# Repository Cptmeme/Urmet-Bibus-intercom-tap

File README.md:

# telefoon_input: Urmet Bibus VOP intercom tap

Reverse-engineering the Urmet intercom (Artico monitor 1705/1 on bracket 1705/954,
Bibus 2nd Ed. VOP) so it can be bridged into Home Assistant.

| Path | What |
|---|---|
| `bus_tap/` | KiCad project for the analog tap board (L1/L2 + C1/C2 to ESP32 ADC), JLCPCB files in `bus_tap/jlc/` |
| `firmware/bus_tap_capture/` | ESP32 firmware streaming the tap's ADC channels over Wi-Fi/UDP |
| `host/` | `bustap`: record, analyse, decode and compare bus traffic |
| `docs/` | Urmet Bibus 2nd Ed. VOP technical manual, section 4B |
| `telefoon_input.kicad_sch` | reverse-engineered schematic of the AliExpress PC817 opto board |

Order of work: build the tap board, flash the firmware, run `bustap monitor` at the wall,
then record and decode. See `host/README.md`.

**Safety.** bus_tap GND is bus L2 and the tap is not isolated. While it is connected to
the intercom, the ESP32 runs from an isolated USB supply and talks over Wi-Fi only.

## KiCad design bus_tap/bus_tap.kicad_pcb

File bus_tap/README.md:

# Urmet Bibus VOP — L1/L2 + C1/C2 analog tap

Front end that lets an ESP32 act as the oscilloscope we don't have, so we can
measure the modulation depth and bit timing on the Urmet door-phone bus.

Target hardware: **Urmet Bibus 2nd Ed. VOP**, Artico monitor Ref. 1705/1 on
bracket Ref. 1705/954. Manual in `../docs/`.

## Wiring

### Intercom side
| Board | Intercom terminal | Note |
|---|---|---|
| J1-1 | **L1** | bus positive (22.5 V idle as measured) |
| J1-2 | **L2** | becomes board GND |
| J2-1 | **C1** | floor call |
| J2-2 | **C2** | floor call |

Leave **VPI / VPU alone.** They carry the monitor's operating power
(700 mA, 16–18.5 Vdc), not just video.

### ESP32 side — J3
| J3 | ESP32 (classic DevKit) | Signal |
|---|---|---|
| 1 | 3V3 | supply for U1 |
| 2 | GND | **= bus L2** |
| 3 | GPIO34 | `ADC_DC`  — channel A, absolute bus voltage |
| 4 | GPIO35 | `ADC_AC`  — channel B, AC-coupled ×11 |
| 5 | GPIO36 (VP) | `ADC_FC` — channel C, floor call |

**Use ADC1 pins only.** ADC2 is unusable while Wi-Fi is on, and we need Wi-Fi
(see safety note below). GPIO34/35/36 are input-only, which suits analog.

## Channels

- **A — absolute.** R1/R2 divide by 11, U1A buffers, R3/C1 anti-alias at ~16 kHz.
  Window 0–34 V, so 22.5 V idle sits at 2.05 V. Shows big dips and the DC level.
- **B — AC-coupled, gain 11.** C2 blocks DC, R4/R5 re-bias to 1.65 V, U1B gains
  ×11. Net effect: **1 V of bus swing = 1 V at the ADC**, centred on 1.65 V,
  ±1.5 V before clipping, 3.2 Hz high-pass. This is the channel that will show
  small modulation and edges that channel A buries in quantisation noise.
- **C — floor call.** Same divider + buffer on C1/C2.

MCP6004 is CMOS (~1 pA bias), so the 1 MΩ divider costs ~1 µV of offset. Do not
substitute a bipolar op-amp such as LM324 — it is neither rail-to-rail nor
happy at 3.3 V, and its bias current would swamp the divider.

## Connector notes

There is **no separate external GND**. Board GND *is* bus L2 - it arrives on J1-2 and
leaves on J3-2 to the ESP32. Do not add a dedicated ground pin; the one thing this
board must not have is two references.

Mis-plugging is harmless: both bus channels use identical 1M/100k front ends, so
swapping the L1/L2 and C1/C2 headers does nothing bad, and reversing L1/L2 polarity
merely pins channel A at zero (D1 clamps at -0.3 V, the 1 M holds current to ~22 uA).

The one real risk is a wire that works loose and *dangles* behind the intercom, where
it could bridge L1 to L2. A disconnected tap is harmless - it is passive and
high-impedance, you just lose data - but a flapping conductor on a shared bus is not.
Use short leads with heat-shrink strain relief, or fit keyed/latching connectors
(JST-XH is 2.54 mm pitch, polarised, and JLC-stocked) if you want it fit-and-forget.

## Safety

1. **This tap is NOT isolated** — board GND is bus L2. Power the ESP32 from an
   isolated USB wall wart and get data off over **Wi-Fi/UDP**. Never plug the
   laptop's USB in while J1 is connected to the bus; that would tie the
   building's bus rail to your laptop's ground.
2. **Bus loading:** 22.5 V / 1.1 MΩ ≈ **20 µA**. The manual specs the whole
   monitor's standby draw on L1/L2 as **1.6 mA max**, so this tap is ~1.3% of
   it. This is why the PC817 opto board must not go here — at 3.3 kΩ it would
   draw 5.9 mA, ~3.7× the entire monitor.
3. **JP1** links C2 to board GND. Fit it **only** after confirming with a
   multimeter that the C1/C2 loop shares a reference with L2. If that loop
   floats, leave JP1 open and sense C1/C2 with the separate opto board — C1/C2
   is local to this monitor only, so nothing there can affect neighbours.

## JLCPCB part status

Checked against JLCPCB's Economic Parts list (Basic + Preferred Extended = $0 feeder
fee). Everything below is in that list **except** the three noted.

| Part | LCSC | Library | Note |
|---|---|---|---|
| R 1k 0402 | C11702 | Basic | |
| R 10k 0402 | C25744 | Basic | |
| R 100k 0402 | C25741 | Basic | |
| R 1M 0805 | C17514 | Basic | **150 V rated** |
| C 10n 0402 | C15195 | Basic | |
| C 100n 0402 | C1525 | Basic | |
| C 1u 0402 | C52923 | Basic | |
| C 10u 0402 | C15525 | Basic | 6.3 V X5R |
| BAT54S SOT-23 | C7420333 | Preferred Ext. | $0 fee, 1.2 M in stock |
| MCP6004T-I/SL | C7378 | **Extended** | feeder fee |
| 2.54 mm 1x02 header | - | **Extended** | no connectors are economic parts |
| 2.54 mm 1x05 header | - | **Extended** | " |

**3 unique Extended parts -> roughly $9 in one-off feeder fees.**

Why R1/R9 stay 0805: the 0402 1M (C26083) is rated **50 V**, the 0805 1M (C17514)
is **150 V**. R1/R9 take 10/11 of anything appearing on L1/L2, and the door strike
is inductive. This is the one place the extra millimetre is worth it.

### Cutting the feeder fees to zero

1. **Hand-solder the four headers.** They are the only through-hole parts and the
   only reason to pay for THT assembly at all. Removes 2 of the 3 Extended parts.
2. **Swap the quad for 2x MCP6002 (C7377, Preferred Extended, $0).** Two SOIC-8
   instead of one SOIC-14. Only 3 of the 4 amplifiers are used, so two duals give
   the same single spare. Costs a schematic edit and one more decoupling cap.

### Do NOT substitute LM324

`LM324DT` (C71035) is a Basic part, SOIC-14, and pin-compatible with the MCP6004.
It will not work here. Its input common-mode range is Vee to Vcc-1.5 V, i.e. 0 to
**1.8 V** on a 3.3 V rail - but channel A's input sits at **2.05 V**, outside that
range entirely. Its 45 nA input bias across the 90.9 kOhm source would also add
several mV of offset where the MCP6004's ~1 pA adds a microvolt. Same footprint,
free, and completely wrong.

## Files

| File | Purpose |
|---|---|
| `bom.csv` | full engineering BOM (refs, values, footprints, LCSC, JLC library) |
| `bom_jlcpcb.csv` | **upload this to JLCPCB** - Comment / Designator / Footprint / LCSC Part #, SMD only |
| `bus_tap.pdf` | schematic print |
| `erc.rpt` | ERC report |

`bom_jlcpcb.csv` covers 21 assembled parts over 10 lines. J1, J2, J3 and JP1 are
deliberately excluded - they are the only through-hole parts, they are the only
Extended parts left once the MCP6004 fee is paid, and hand-fitting four headers takes
minutes. Designators are written as explicit lists (`R2,R4,R5,R6,R10`), not KiCad's
default ranges (`R4-R6`), which JLC's BOM parser does not understand.

Each symbol carries `LCSC` and `JLC` fields, so both BOMs regenerate straight from
the schematic.

## JLCPCB upload files (`jlc/`)

| File | Upload as |
|---|---|
| `bus_tap-gerbers.zip` | PCB (11 fab layers, gerber drill included) |
| `bom_jlc.csv` | BOM - `Comment / Designator / Footprint / LCSC Part #` |
| `cpl_jlc.csv` | CPL - `Designator / Mid X / Mid Y / Layer / Rotation` |

J1, J2, J3 and JP1 are excluded from both CSVs (hand-soldered). BOM and CPL
designators cross-check: 21 each, no orphans.

### CPL rotation corrections - ALREADY APPLIED to cpl_jlc.csv

JLC's library orientation differs from KiCad's for two packages here. Determined
empirically from JLC's upload preview, and **baked into `cpl_jlc.csv`**:

| Part | Package | KiCad rot | Correction | CPL value |
|---|---|---|---|---|
| D1 | SOT-23 | 0 | +180 | **180** |
| D2 | SOT-23 | 180 | +180 | **0** |
| U1 | SOIC-14 | 0 | -90 (90 CW) | **270** |

Rotation in the CPL is **counter-clockwise-positive**, matching KiCad's own pos file
(which emits -90 for C6/C7 and +90 for R10). KiCad places SOIC-14 with the long axis
vertical and pin 1 top-left; JLC's library has it horizontal, hence the 90 deg.

The 18 chip R/C parts need no correction - they are two-terminal and non-polarised,
so 0 vs 180 is electrically identical.

**Verification on next upload: the preview should need NO manual rotation.** If any of
these three still looks wrong, the correction above is stale - re-derive it rather than
nudging it in the preview.

## Status

- Schematic: complete, hand-tidied in eeschema, **ERC clean (0 violations)**, netlist verified unchanged.
- Footprints: **assigned on all 25 parts**, 9 distinct footprints, all verified present in the KiCad libraries.
- PCB: not started. Target is JLCPCB Economic PCBA. Run **Tools > Update PCB from Schematic (F8)** in the PCB editor to seed it.

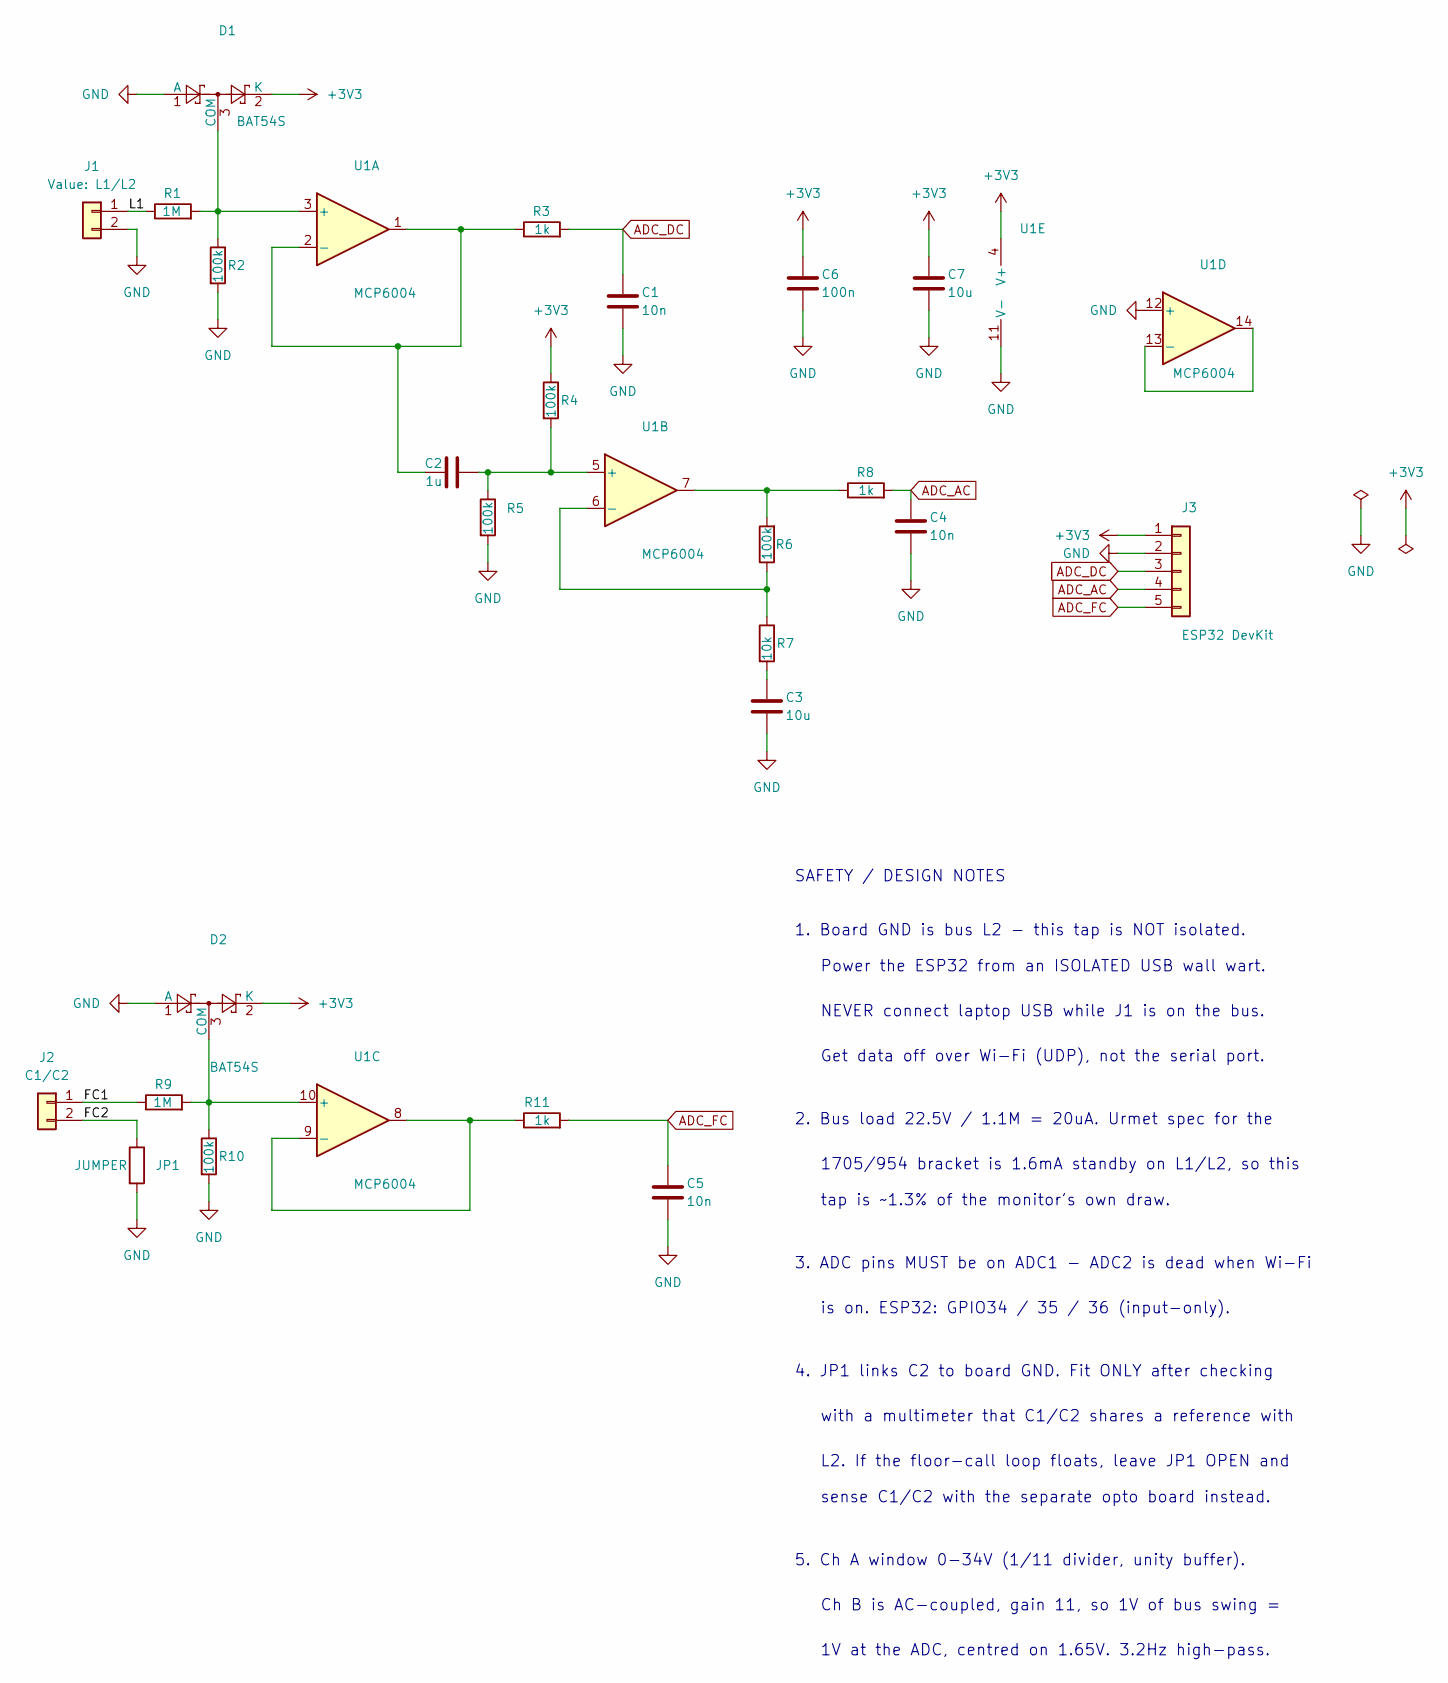
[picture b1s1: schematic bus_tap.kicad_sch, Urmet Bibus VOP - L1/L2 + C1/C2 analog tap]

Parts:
C1, C4, C5: 10n; C_0402_1005Metric; LCSC C15195
C2: 1u; C_0402_1005Metric; LCSC C52923
C3, C7: 10u; C_0402_1005Metric; LCSC C15525
C6: 100n; C_0402_1005Metric; LCSC C1525
D1, D2: BAT54S; SOT-23; LCSC C7420333
J1: L1/L2; PinHeader_1x02_P2.54mm_Vertical; JLC Extended - hand solder, not in JLC BOM
J2: C1/C2; PinHeader_1x02_P2.54mm_Vertical; JLC Extended - hand solder, not in JLC BOM
J3: ESP32 DevKit; PinHeader_1x05_P2.54mm_Vertical; JLC Extended - hand solder, not in JLC BOM
JP1: JUMPER; PinHeader_1x02_P2.54mm_Vertical; JLC Extended - hand solder, not in JLC BOM
R1, R9: 1M; R_0805_2012Metric; LCSC C17514
R2, R4, R5, R6, R10: 100k; R_0402_1005Metric; LCSC C25741
R3, R8, R11: 1k; R_0402_1005Metric; LCSC C11702
R7: 10k; R_0402_1005Metric; LCSC C25744
U1: MCP6004; SOIC-14_3.9x8.7mm_P1.27mm; LCSC C7378

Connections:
+3V3: C6.1, C7.1, D1.2 (K), D2.2 (K), J3.1, R4.1, U1.4 (V+)
/FC1: J2.1, R9.1
/FC2: J2.2, JP1.1
/L1: J1.1, R1.1
ADC_AC: C4.1, J3.4, R8.2
ADC_DC: C1.1, J3.3, R3.2
ADC_FC: C5.1, J3.5, R11.2
GND: C1.2, C3.2, C4.2, C5.2, C6.2, C7.2, D1.1 (A), D2.1 (A), J1.2, J3.2, JP1.2, R2.2, R5.2, R10.2, U1.11 (V-), U1.12 (+)
unnamed: C3.1, R7.2
unnamed: D1.3 (COM), R1.2, R2.1, U1.3 (+)
unnamed: D2.3 (COM), R9.2, R10.1, U1.10 (+)
unnamed: R6.2, R8.1, U1.7
unnamed: C2.1, R3.1, U1.1, U1.2 (-)
unnamed: C2.2, R4.2, R5.1, U1.5 (+)
unnamed: R6.1, R7.1, U1.6 (-)
unnamed: R11.1, U1.8, U1.9 (-)
unnamed: U1.13 (-), U1.14

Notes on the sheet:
Ch B is AC-coupled, gain 11, so 1V of bus swing =
tap is ~1.3% of the monitor's own draw.
4. JP1 links C2 to board GND. Fit ONLY after checking
Power the ESP32 from an ISOLATED USB wall wart.
L2. If the floor-call loop floats, leave JP1 OPEN and
NEVER connect laptop USB while J1 is on the bus.
2. Bus load 22.5V / 1.1M = 20uA. Urmet spec for the
Get data off over Wi-Fi (UDP), not the serial port.
3. ADC pins MUST be on ADC1 - ADC2 is dead when Wi-Fi
1V at the ADC, centred on 1.65V. 3.2Hz high-pass.
1705/954 bracket is 1.6mA standby on L1/L2, so this
SAFETY / DESIGN NOTES
1. Board GND is bus L2 - this tap is NOT isolated.
sense C1/C2 with the separate opto board instead.
is on. ESP32: GPIO34 / 35 / 36 (input-only).
with a multimeter that C1/C2 shares a reference with
5. Ch A window 0-34V (1/11 divider, unity buffer).

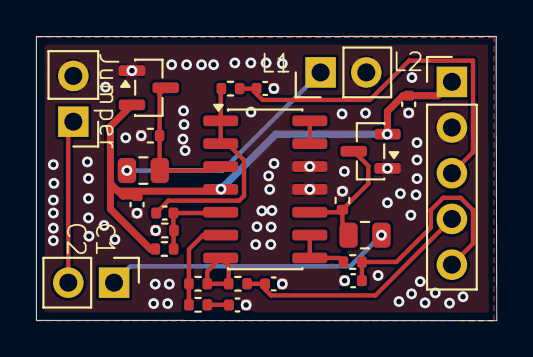
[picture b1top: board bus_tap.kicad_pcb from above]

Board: 2 copper layers, 25.6 x 15.8 mm, 25 parts (0 on the bottom side), 17 nets.

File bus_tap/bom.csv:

"Reference","Value","Footprint","LCSC"
"C1,C4,C5","10n","Capacitor_SMD:C_0402_1005Metric","C15195"
"C2","1u","Capacitor_SMD:C_0402_1005Metric","C52923"
"C3,C7","10u","Capacitor_SMD:C_0402_1005Metric","C15525"
"C6","100n","Capacitor_SMD:C_0402_1005Metric","C1525"
"D1,D2","BAT54S","Package_TO_SOT_SMD:SOT-23","C7420333"
"J1","L1/L2","Connector_PinHeader_2.54mm:PinHeader_1x02_P2.54mm_Vertical",""
"J2","C1/C2","Connector_PinHeader_2.54mm:PinHeader_1x02_P2.54mm_Vertical",""
"J3","ESP32 DevKit","Connector_PinHeader_2.54mm:PinHeader_1x05_P2.54mm_Vertical",""
"JP1","JUMPER","Connector_PinHeader_2.54mm:PinHeader_1x02_P2.54mm_Vertical",""
"R1,R9","1M","Resistor_SMD:R_0805_2012Metric","C17514"
"R2,R4-R6,R10","100k","Resistor_SMD:R_0402_1005Metric","C25741"
"R3,R8,R11","1k","Resistor_SMD:R_0402_1005Metric","C11702"
"R7","10k","Resistor_SMD:R_0402_1005Metric","C25744"
"U1","MCP6004","Package_SO:SOIC-14_3.9x8.7mm_P1.27mm","C7378"
